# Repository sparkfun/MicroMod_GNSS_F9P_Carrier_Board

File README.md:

SparkFun MicroMod GNSS Carrier Board (ZED-F9P)
========================================

[*SparkFun MicroMod GNSS Carrier Board (ZED-F9P) (GPS-17722)*](https://www.sparkfun.com/products/17722)

With GNSS you are able to know where you are, where you're going, and how to get there anywhere on Earth within 30 seconds. This means the higher the accuracy the better! GNSS Real Time Kinematics (RTK) has mastered dialing in the accuracy of their GNSS modules to just millimeters, and that's why we had to put it on this board! With the flexibility of the MicroMod's M.2 connector, you can easily test and swap out different MicroMod processor boards for your application. Simply match up the key on your board's beveled edge connector to the key on the M.2 connector and secure the boards with a screw.

The SparkFun MicroMod GNSS Carrier Board raises the bar for high-precision GPS and is in a line of powerful RTK boards featuring the ZED-F9P module from u-blox. The ZED-F9P is a top-of-the-line module for high accuracy GNSS and GPS location solutions including RTK that is capable of 10mm, three-dimensional accuracy. With this board, you will be able to know where your (or any object's) X, Y, and Z location is within roughly the width of your fingernail! The ZED-F9P is unique in that it is capable of both rover and base station operations. Utilizing the M.2 and Qwiic connectors, no soldering is required to connect it to the rest of your system. However, we still broke out 0.1"-spaced pins in case you prefer to use a breadboard to attach additional peripherals.

The board includes two USB-C connectors for power and programming. Two buttons for reset and boot are also populated on the board. A 2A resettable fuse and 3.3V/1A voltage regulator are built-in to the board for power. We've even added a convenient jumper for advanced users looking to bypass the fuse and another to measure the current consumption for low power testing. Five status LEDs are available for power, 3.3V, PPS, RTK, and geofencing. These can also be disabled via the jumper pads. One SMA connector is included for a secure connection to an antenna. For those that need a secure connection to the PPS pin, the SMA connector footprint is included in the design so that you can manually solder it to the board for your application. Finally, one Qwiic connector is populated on the board to easily add Qwiic enabled I<sup>2</sup>C devices to your projects!

We've even included a rechargeable backup battery to keep the latest module configuration and satellite data available for up to two weeks. This battery helps 'warm-start' the module, decreasing the time-to-first-fix dramatically. This module features a survey-in mode allowing the module to become a base station and produce RTCM 3.x correction data.

The number of configuration options of the ZED-F9P is incredible! Geofencing, variable I<sup>2</sup>C address, variable update rates, even the high precision RTK solution can be increased to 20Hz. The MicroMod GNSS carrier board even has five communications ports, four of which are all active simultaneously: USB-C (which enumerates as a COM port), UART1 (with 3.3V TTL), UART2 for RTCM reception (with 3.3V TTL), I<sup>2</sup>C (via the one Qwiic connector or broken out pins), and SPI.

We've also written an extensive [Arduino library for u-blox modules](https://github.com/sparkfun/SparkFun_u-blox_GNSS_Arduino_Library) to make reading and controlling the MicroMod GNSS carrier board over the MicroMod's I<sup>2</sup>C bus is easy. Leave NMEA behind! Start using a much lighter weight binary interface and give your microcontroller (and its one serial port) a break. The SparkFun Arduino library shows how to read latitude, longitude, even heading and speed over I<sup>2</sup>C without the need for constant serial polling.

Repository Contents
-------------------

* **/Hardware** - Eagle design files (.brd, .sch)
* **/Production** - Production panel files (.brd)

Documentation
--------------
* **[Library](https://github.com/sparkfun/SparkFun_u-blox_GNSS_Arduino_Library)** - Arduino library for the u-blox modules (e.g. ZED-F9P)
* **[Hookup Guide](https://learn.sparkfun.com/tutorials/2187)** - Basic hookup guide for the ZED-F9P Carrier Board

Product Versions
----------------
* [GPS-17722](https://www.sparkfun.com/products/17722) 

Version History
---------------
* v1.0 - initial release

License Information
-------------------

This product is _**open source**_! 

Please review the LICENSE.md file for license information. 

If you have any questions or concerns on licensing, please contact technical support on our [SparkFun forums](https://forum.sparkfun.com/viewforum.php?f=152).

Distributed as-is; no warranty is given.

- Your friends at SparkFun.

_<COLLABORATION CREDIT>_

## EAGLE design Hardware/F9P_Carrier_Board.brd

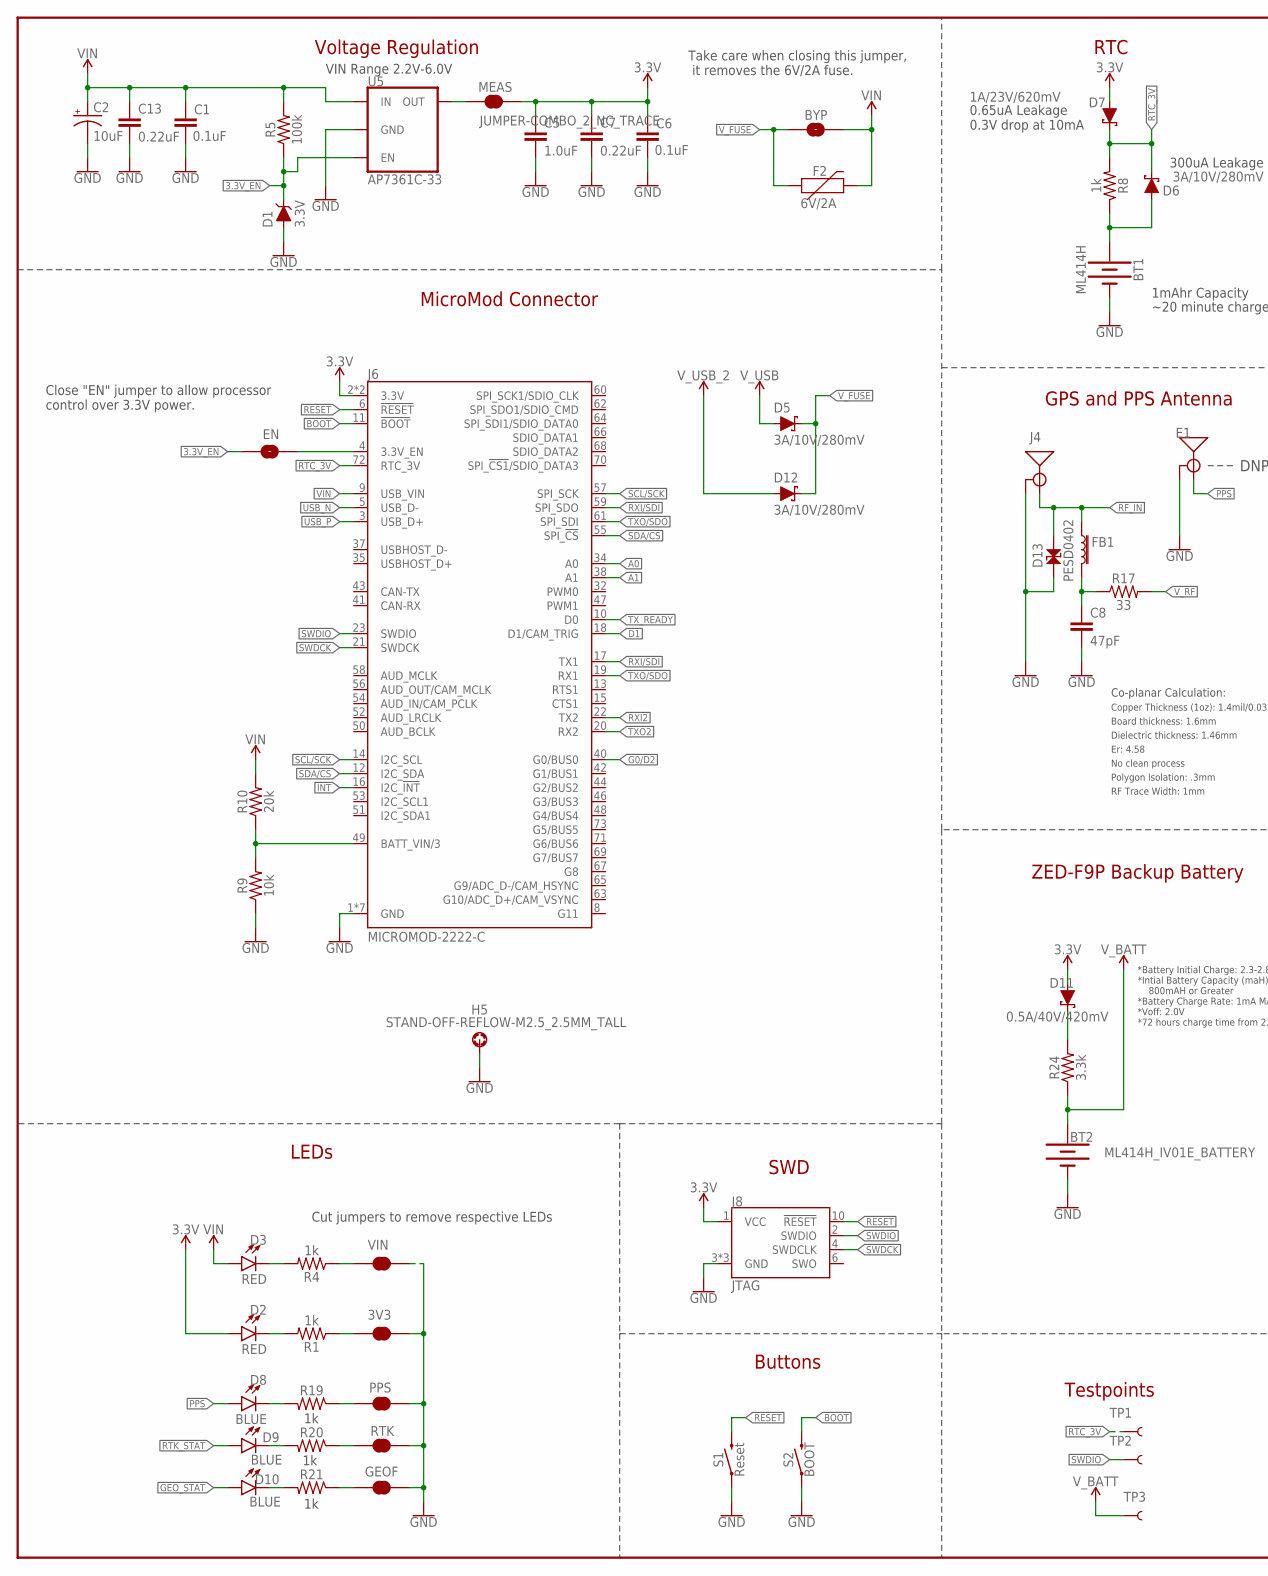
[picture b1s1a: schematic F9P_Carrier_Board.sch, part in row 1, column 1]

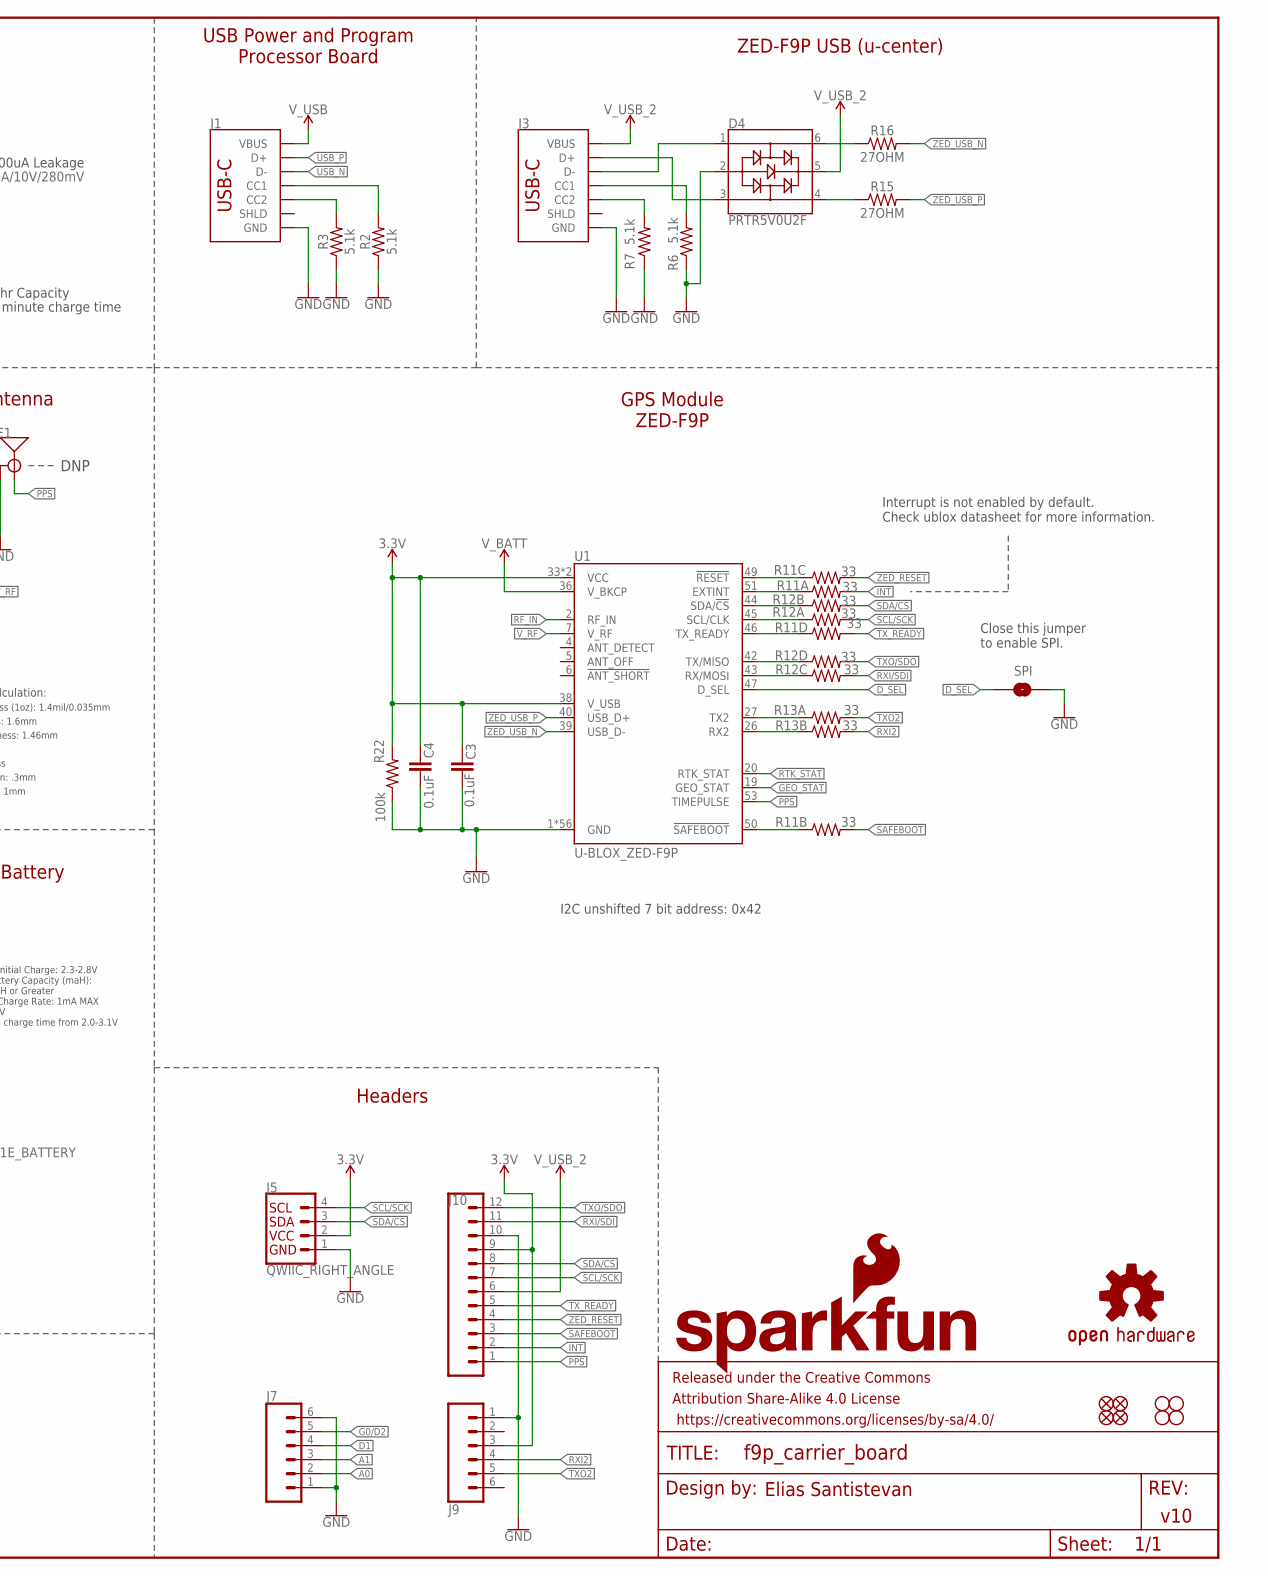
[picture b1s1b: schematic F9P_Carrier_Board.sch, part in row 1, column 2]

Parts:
3V3: JUMPER-SMT_2_NC_TRACE_SILK; SMT-JUMPER_2_NC_TRACE_SILK
BT1: ML414H; ML414H_IV01E
BT2: ML414H_IV01E_BATTERY; ML414H_IV01E
BYP: JUMPER-SMT_2_NO_SILK; SMT-JUMPER_2_NO_SILK
C1, C3, C4, C6: 0.1uF; 0603
C2: 10uF; EIA3216
C5: 1.0uF; 0603
C7, C13: 0.22uF; 0603
C8: 47pF; 0603
D1: 3.3V; SOD-323
D2, D3: RED; LED-0603
D4: PRTR5V0U2F; SOT886
D5, D6, D12: 3A/10V/280mV; SOD-323
D7: 1A/23V/620mV; SOD-323
D8, D9, D10: BLUE; LED-0603
D11: 0.5A/40V/420mV; SOD-323
D13: PESD0402; 0402
E1: ANTENNA-SMA-GROUNDEDEDGE_SMA; SMA-EDGE
EN: JUMPER-SMT_2_NO_SILK; SMT-JUMPER_2_NO_SILK
F2: 6V/2A; 1210
FB1: FERRITE_BEAD-120_OHM-0402T; 0402-TIGHT
FD1, FD2, FD3, FD4: FIDUCIALUFIDUCIAL; FIDUCIAL-MICRO
FRAME1: FRAME-LEDGER; CREATIVE_COMMONS
GEOF: JUMPER-SMT_2_NC_TRACE_SILK; SMT-JUMPER_2_NC_TRACE_SILK
H1, H2, H3, H4: STAND-OFFTIGHT; STAND-OFF-TIGHT
H5: STAND-OFF-REFLOW-M2.5_2.5MM_TALL; STAND-OFF-REFLOW-M2.5
J1, J3: USB_C_2-LAYER_PADS; USB-C-16P-2LAYER-PADS
J4: U.FL; SMA-EDGE
J5: QWIIC_RIGHT_ANGLE; JST04_1MM_RA
J6: MICROMOD-2222-C; M.2-CONNECTOR-E
J7, J9: CONN_06NO_SILK_NO_POP; 1X06_NO_SILK
J8: JTAG; 2X5-PTH-1.27MM
J10: CONN_12NO_SILK; 1X12_NO_SILK
LOGO1: SFE_LOGO_NAME_FLAME.3_INCH; SFE_LOGO_NAME_FLAME_.3
LOGO3: OSHW-LOGOMINI; OSHW-LOGO-MINI
MEAS: JUMPER-COMBO_2_NC_TRACE; COMBO-JUMPER_2_NC_TRACE
PPS: JUMPER-SMT_2_NC_TRACE_SILK; SMT-JUMPER_2_NC_TRACE_SILK
R1, R4, R8, R19, R20, R21: 1k; 0603
R2, R3, R6, R7: 5.1k; 0603
R5, R22: 100k; 0603
R9: 10k; 0603
R10: 20k; 0603
R11, R12, R13: 33; 1206_RA
R15, R16: 27OHM; 0402-TIGHT
R17: 33; 0603
R24: 3.3k; 0603
RTK: JUMPER-SMT_2_NC_TRACE_SILK; SMT-JUMPER_2_NC_TRACE_SILK
S1: Reset; TACTILE_SWITCH_SMD_5.2MM
S2: BOOT; TACTILE_SWITCH_SMD_5.2MM
SPI: JUMPER-SMT_2_NO_SILK; SMT-JUMPER_2_NO_SILK
TP1, TP2, TP3: TEST-POINT3X5; PAD.03X.05
U1: U-BLOX_ZED-F9P; ZED-F9P
U5: AP7361C-33; UDFN-8
VIN: JUMPER-SMT_2_NC_TRACE_SILK; SMT-JUMPER_2_NC_TRACE_SILK

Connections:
3.3V: C3.1, C4.1, C5.1, C6.1, C7.1, D2.A, D7.A, D11.A, J5.2, J6.2 (3.3V), J6.74 (3.3V), J8.1 (VCC), J9.3, J10.9, MEAS.2, MEAS.4 (2), R22.2, U1.33 (VCC), U1.34 (VCC), U1.38 (V_USB)
3.3V_EN: D1.C, EN.1, R5.1, U5.5 (EN)
!BOOT!: J6.11 (!BOOT!), S2.3 (2), S2.4 (2)
!RESET!: J6.6 (!RESET!), J8.10 (!RESET), S1.3 (2), S1.4 (2)
!SAFEBOOT!: J10.3, R11.P7 (2)
!ZED_RESET!: J10.4, R11.P6 (2)
A0: J6.34 (A0), J7.2
A1: J6.38 (A1), J7.3
D1: J6.18 (D1/CAM_TRIG), J7.4
D_SEL: SPI.1, U1.47 (D_SEL)
G0/D2: J6.40 (G0/BUS0), J7.5
GEO_STAT: D10.A, U1.19 (GEO_STAT)
GND: 3V3.2, BT1.-, BT2.-, C1.2, C2.-, C3.2, C4.2, C5.2, C6.2, C7.2, C8.2, C13.2, D1.A, D4.2, D13.1, E1.GND@0 (GND), E1.GND@1 (GND), E1.GND@2 (GND), E1.GND@3 (GND), GEOF.1, H5.1, J1.GND, J1.GND2 (GND), J3.GND, J3.GND2 (GND), J4.GND@0 (GND), J4.GND@1 (GND), J4.GND@2 (GND), J4.GND@3 (GND), J5.1, J6.1 (GND), J6.7 (GND), J6.33 (GND), J6.36 (GND), J6.39 (GND), J6.45 (GND), J6.75 (GND), J7.1, J7.6, J8.3 (GND), J8.5 (GND), J8.9 (GND), J9.1, J10.10, PPS.1, R2.1, R3.1, R6.1, R7.1, R9.1, R22.1, RTK.1, S1.1, S1.2 (1), S2.1, S2.2 (1), SPI.2, U1.1 (GND), U1.3 (GND), U1.12 (GND), U1.14 (GND), U1.32 (GND), U1.37 (GND), U1.41 (GND), U1.48 (GND), U1.55 (GND), U1.56 (GND), U1.57 (GND), U1.58 (GND), U1.59 (GND), U1.60 (GND), U1.61 (GND), U1.62 (GND), U1.63 (GND), U1.64 (GND), U1.65 (GND), U1.66 (GND), U1.67 (GND), U1.68 (GND), U1.69 (GND), U1.70 (GND), U1.71 (GND), U1.72 (GND), U1.73 (GND), U1.74 (GND), U1.75 (GND), U1.76 (GND), U1.77 (GND), U1.78 (GND), U1.79 (GND), U1.80 (GND), U1.81 (GND), U1.82 (GND), U1.83 (GND), U1.84 (GND), U1.85 (GND), U1.86 (GND), U1.87 (GND), U1.88 (GND), U1.89 (GND), U1.90 (GND), U1.91 (GND), U1.92 (GND), U1.93 (GND), U1.94 (GND), U1.95 (GND), U1.96 (GND), U1.97 (GND), U1.98 (GND), U1.99 (GND), U1.100 (GND), U1.101 (GND), U1.102 (GND), U5.4 (GND), U5.EP (GND), VIN.2
INT: J6.16 (I2C_!INT!), J10.2, R11.P8 (2)
unnamed: D2.C, R1.2
unnamed: R4.1, VIN.1
unnamed: 3V3.1, R1.1
unnamed: D3.C, R4.2
unnamed: EN.2, J6.4 (3.3V_EN)
unnamed: J3.A5 (CC1), R6.2
unnamed: J3.B5 (CC2), R7.2
unnamed: R20.1, RTK.2
unnamed: D4.6, R16.1
unnamed: J1.A5 (CC1), R2.2
unnamed: J1.B5 (CC2), R3.2
unnamed: D4.3, J3.A6 (D+), J3.B6 (D+)
unnamed: D4.1, J3.A7 (D-), J3.B7 (D-)
unnamed: BT1.+, D6.A, R8.1
unnamed: R11.P1 (1), U1.51 (EXTINT)
unnamed: R11.P2 (1), U1.50 (!SAFEBOOT!)
unnamed: D4.4, R15.1
unnamed: C8.1, FB1.2, R17.1
unnamed: R11.P3 (1), U1.49 (!RESET!)
unnamed: R11.P4 (1), U1.46 (TX_READY)
unnamed: R12.P1 (1), U1.45 (SCL/CLK)
unnamed: R12.P2 (1), U1.44 (SDA/!CS!)
unnamed: R12.P3 (1), U1.43 (RX/MOSI)
unnamed: R12.P4 (1), U1.42 (TX/MISO)
unnamed: R13.P1 (1), U1.27 (TX2)
unnamed: R13.P2 (1), U1.26 (RX2)
unnamed: PPS.2, R19.1
unnamed: D8.C, R19.2
unnamed: D9.C, R20.2
unnamed: D11.C, R24.2
unnamed: GEOF.2, R21.1
unnamed: D10.C, R21.2
OUT_MEAS: MEAS.1, MEAS.3 (1), U5.1 (OUT)
PPS: D8.A, E1.SIG (SIGNAL), J10.1, U1.53 (TIMEPULSE)
RF_IN: D13.2, FB1.1, J4.SIG (SIGNAL), U1.2 (RF_IN)
RTC_3V: D6.C, D7.C, J6.72 (RTC_3V), R8.2, TP1.1
RTK_STAT: D9.A, U1.20 (RTK_STAT)
RXI2: J6.22 (TX2), J9.4, R13.P7 (2)
RXI/SDI: J6.17 (TX1), J6.59 (SPI_SDO), J10.11, R12.P6 (2)
SCL/SCK: J5.4, J6.14 (I2C_SCL), J6.57 (SPI_SCK), J10.7, R12.P8 (2)
SDA/!CS!: J5.3, J6.12 (I2C_SDA), J6.55 (SPI_!CS!), J10.8, R12.P7 (2)
SWDCK: J6.21 (SWDCK), J8.4 (SWDCLK)
SWDIO: J6.23 (SWDIO), J8.2 (SWDIO), TP2.1
TXO2: J6.20 (RX2), J9.5, R13.P8 (2)
TXO/SDO: J6.19 (RX1), J6.61 (SPI_SDI), J10.12, R12.P5 (2)
TX_READY: J6.10 (D0), J10.5, R11.P5 (2)
USB_N: J1.A7 (D-), J1.B7 (D-), J6.5 (USB_D-)
USB_P: J1.A6 (D+), J1.B6 (D+), J6.3 (USB_D+)
VIN: BYP.2, C1.1, C2.+, C13.1, D3.A, F2.2, J6.9 (USB_VIN), R5.2, R10.2, U5.8 (IN)
VIN/3: J6.49 (BATT_VIN/3), R9.2, R10.1
V_BATT: BT2.+, R24.1, TP3.1, U1.36 (V_BKCP)
V_FUSE: BYP.1, D5.C, D12.C, F2.1
V_RF: R17.2, U1.7 (V_RF)
V_USB: D5.A, J1.VBUS1 (VBUS), J1.VBUS2 (VBUS)
V_USB_2: D4.5, D12.A, J3.VBUS1 (VBUS), J3.VBUS2 (VBUS), J10.6
ZED_USB_N: R16.2, U1.39 (USB_D-)
ZED_USB_P: R15.2, U1.40 (USB_D+)

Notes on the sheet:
300uA Leakage
0.65uA Leakage 0.3V drop at 10mA
~20 minute charge time
1mAhr Capacity
Take care when closing this jumper, it removes the 6V/2A fuse.
RTC
Voltage Regulation
MicroMod Connector
Elias Santistevan
LEDs
Buttons
VIN Range 2.2V-6.0V
Testpoints
*Battery Initial Charge: 2.3-2.8V *Intial Battery Capacity (maH): 800mAH or Greater *Battery Charge Rate: 1mA MAX *Voff: 2.0V *72 hours charge time from 2.0-3.1V
ZED-F9P Backup Battery
Headers
ZED-F9P USB (u-center)
USB Power and Program Processor Board
v10
GPS and PPS Antenna
GPS Module ZED-F9P
SWD
Board thickness: 1.6mm
Er: 4.58
Copper Thickness (1oz): 1.4mil/0.035mm
RF Trace Width: 1mm
Polygon Isolation: .3mm
No clean process
Dielectric thickness: 1.46mm
Co-planar Calculation:
DNP
Close this jumper to enable SPI.
Cut jumpers to remove respective LEDs
Close "EN" jumper to allow processor control over 3.3V power.
Interrupt is not enabled by default. Check ublox datasheet for more information.
I2C unshifted 7 bit address: 0x42

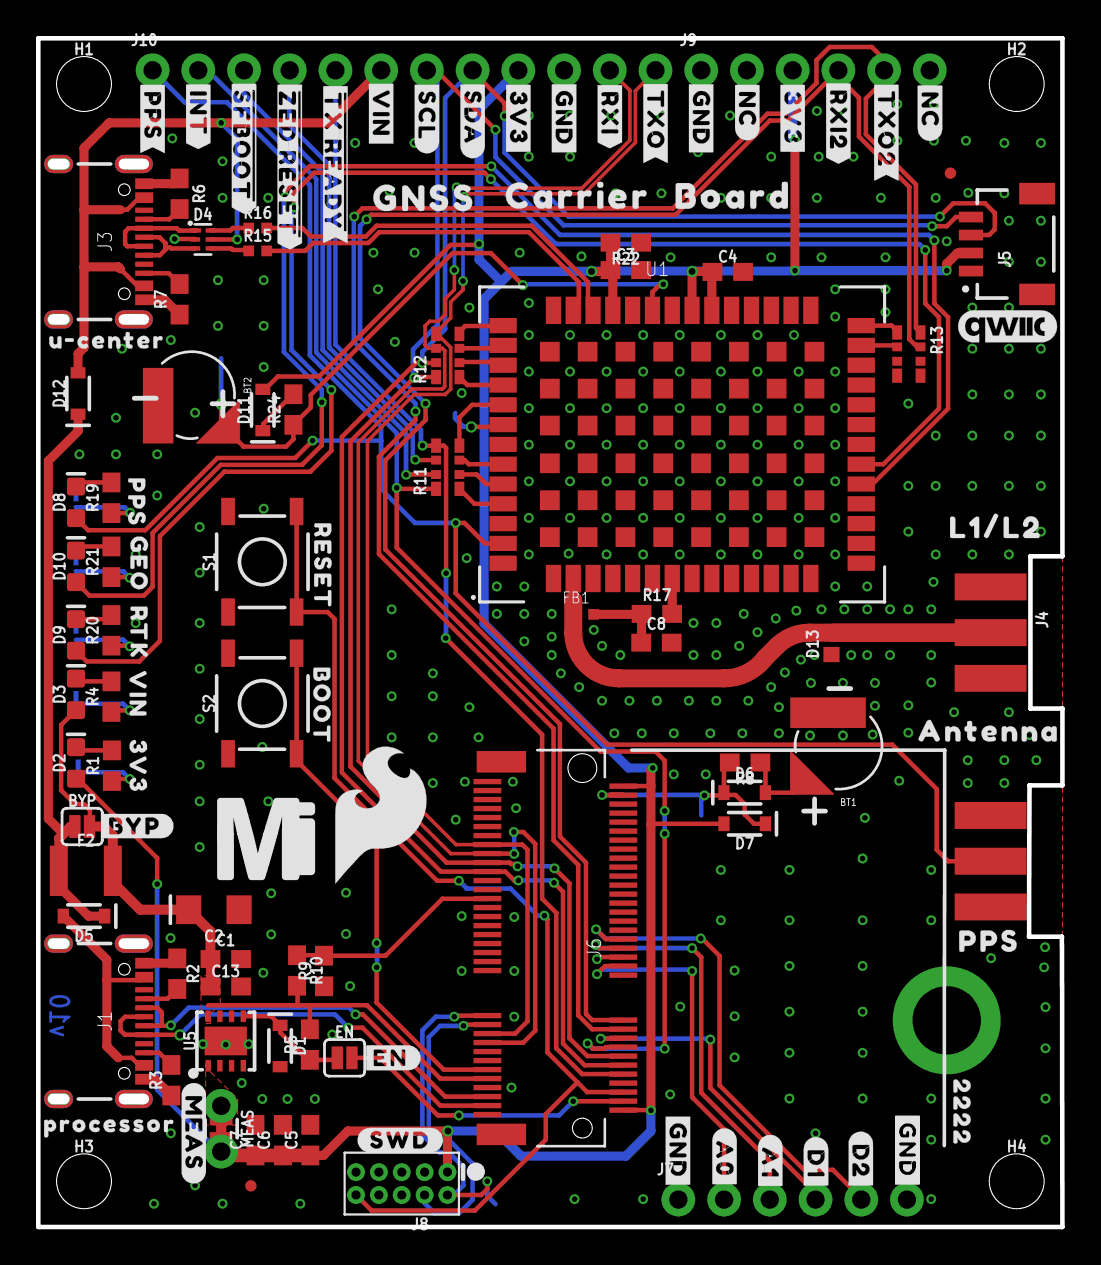
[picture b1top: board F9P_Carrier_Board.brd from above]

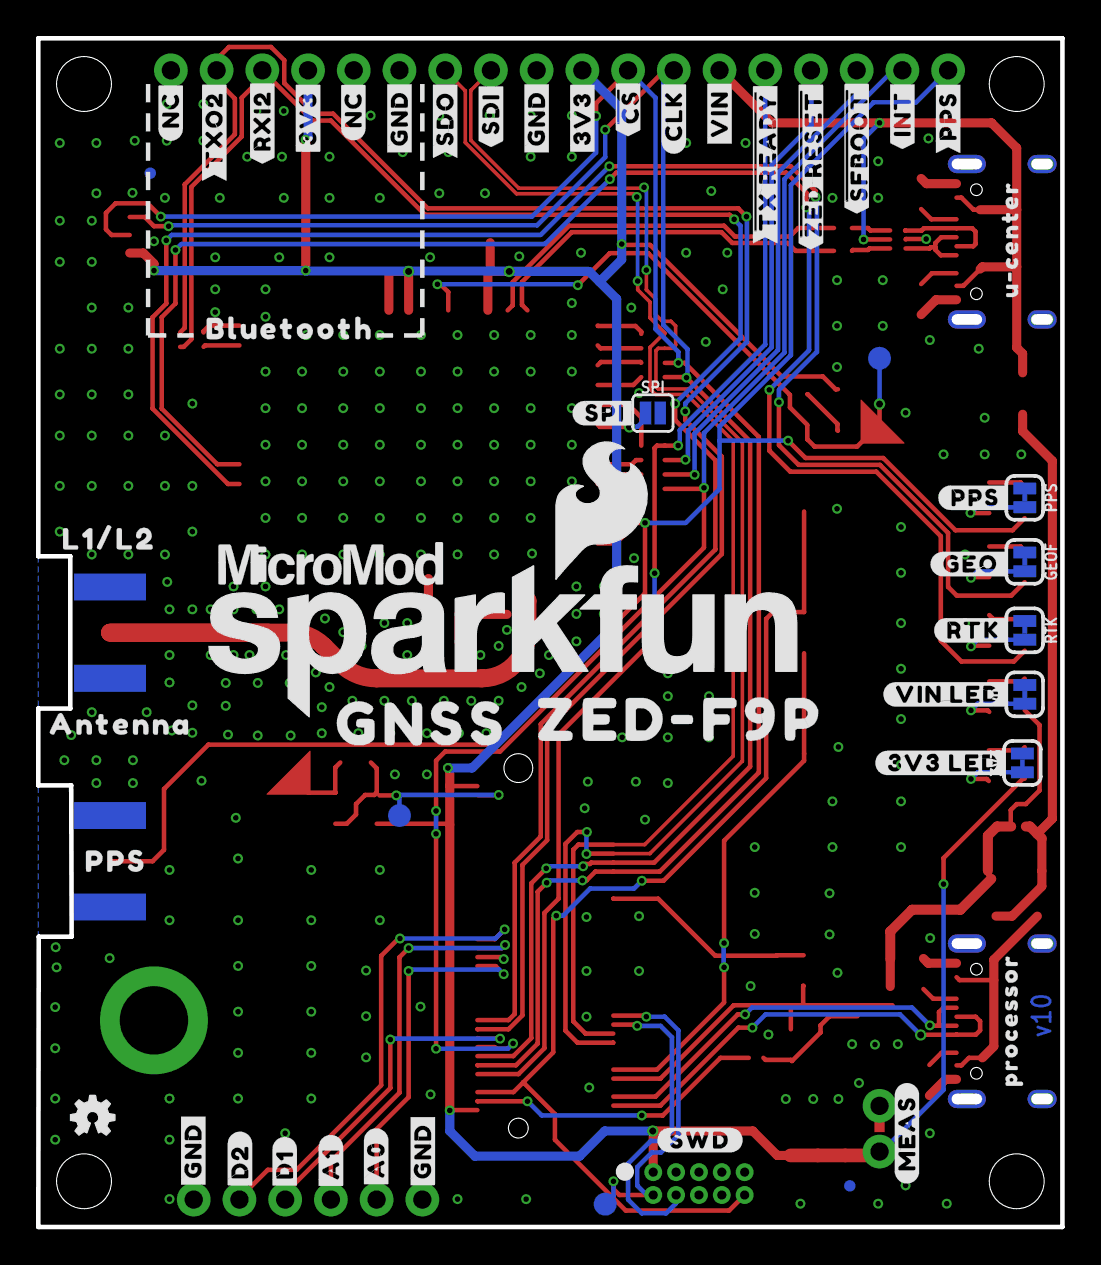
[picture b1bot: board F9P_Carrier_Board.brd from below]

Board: 2 copper layers, 56.9 x 66.0 mm, 174 parts (54 on the bottom side), 71 nets.

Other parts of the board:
U$1: ##SFBOOT##13
U$2: ##SFBOOT##8
U$3, U$4, U$31, U$32: #3V3#1
U$5: #RESET10
U$6, U$7, U$33, U$34, U$64, U$65, U$66, U$77, U$78: #GND#0
U$8: ##TX_READY##13
U$9: #PPS#6
U$10: #SCL#1
U$11: #RXI2#9
U$12: #SDA#0
U$13: #TXO#5
U$14: #RXI#6
U$15: #TXO2#9
U$16: PPS15
U$17, U$35: #VIN#13
U$18: GEO15
U$19: PPS14
U$20: RTK16
U$21: ANTENNA16
U$22: L1#L216
U$23: #GEO#9
U$24: ##TX_READY##7
U$25: MICROMOD_LOGO_.5
U$26: #PPS#10
U$27: #RTK#8
U$28: ##CS##9
U$29: #INT#4
U$30: #SPI#11
U$36: #INT#10
U$37: #PPS#3
U$38: #TXO2#10
U$39: #BYP#8
U$40: #RXI2#10
U$41: MICROMOD_MI_LOGO_1
U$42, U$132: #MEAS#10
U$43: BOOT10
U$44: ZED#F9P19
U$45: GNSS21
U$46: #CLK#7
U$47: #SDO#9
U$48: #EN#0
U$49: U#CENTER20
U$50: QWIIC_5.5MM
U$51, U$131: #SWD#10
U$52, U$73: PROCESSOR23
U$53: #SDI#11
U$54: BLUETOOTH24
U$55, U$83: #NC#4
U$56: U#CENTER22
U$57: #A0#14
U$58: L1#L217
U$59: ANTENNA17
U$60: PPS16
U$61: ##ZED_RESET##9
U$62: ##ZED_RESET##14
U$63: SFE_LOGO_FLAME_.3
U$67: #A0#8
U$68: VIN3
U$69: 3V34
U$70: #A1#8
U$71: #D1#8
U$72: #D2#8
U$74: #A1#14
U$75: #D1#14
U$76: #D2#14
U$79: GNSS501
U$80: CARRIER502
U$81: BOARD503
U$82: 2222501
U$84, U$85: #NC#5
U$133: #VIN_LED#10
U$134: #3V3_LED#10

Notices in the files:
parts and their libraries:
SparkFun-Aesthetics: Licensing: Creative Commons ShareAlike 4.0 International - https://creativecommons.org/licenses/by-sa/4.0
SparkFun-Aesthetics: Released under the Creative Commons Attribution Share-Alike 4.0 License
SparkFun-Aesthetics: https://creativecommons.org/licenses/by-sa/4.0
